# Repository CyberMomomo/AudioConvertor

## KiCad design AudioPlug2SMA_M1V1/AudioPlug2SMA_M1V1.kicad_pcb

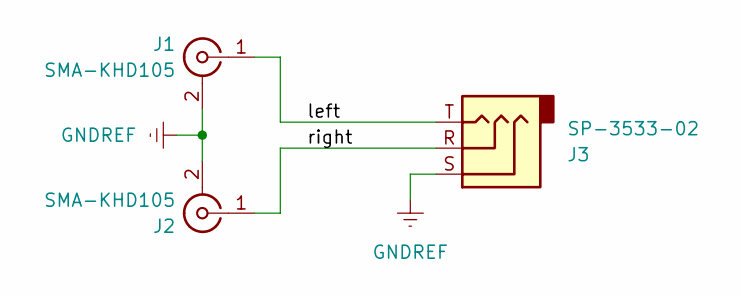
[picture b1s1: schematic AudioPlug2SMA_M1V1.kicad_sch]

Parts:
J1, J2: SMA-KHD105
J3: SP-3533-02

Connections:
/left: J1.1 (In), J3.T
/right: J2.1 (In), J3.R
GNDREF: J1.2 (Ext), J2.2 (Ext), J3.S

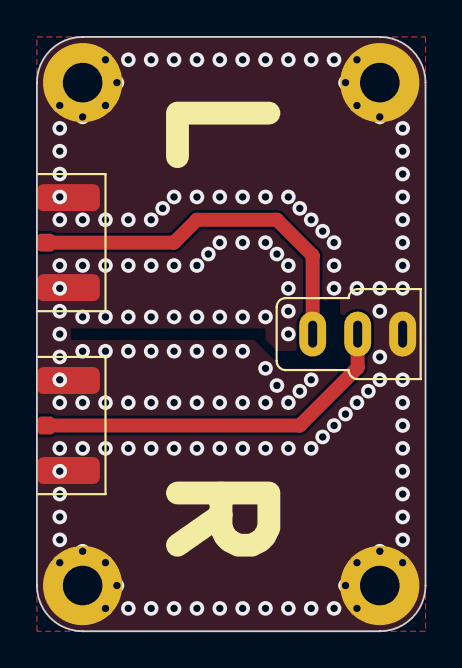
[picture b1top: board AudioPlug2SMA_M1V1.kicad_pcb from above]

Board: 2 copper layers, 21.6 x 33.0 mm, 3 parts (0 on the bottom side), 3 nets.

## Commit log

2023-10-20 Update AudioPlug2SMA_M1V1
